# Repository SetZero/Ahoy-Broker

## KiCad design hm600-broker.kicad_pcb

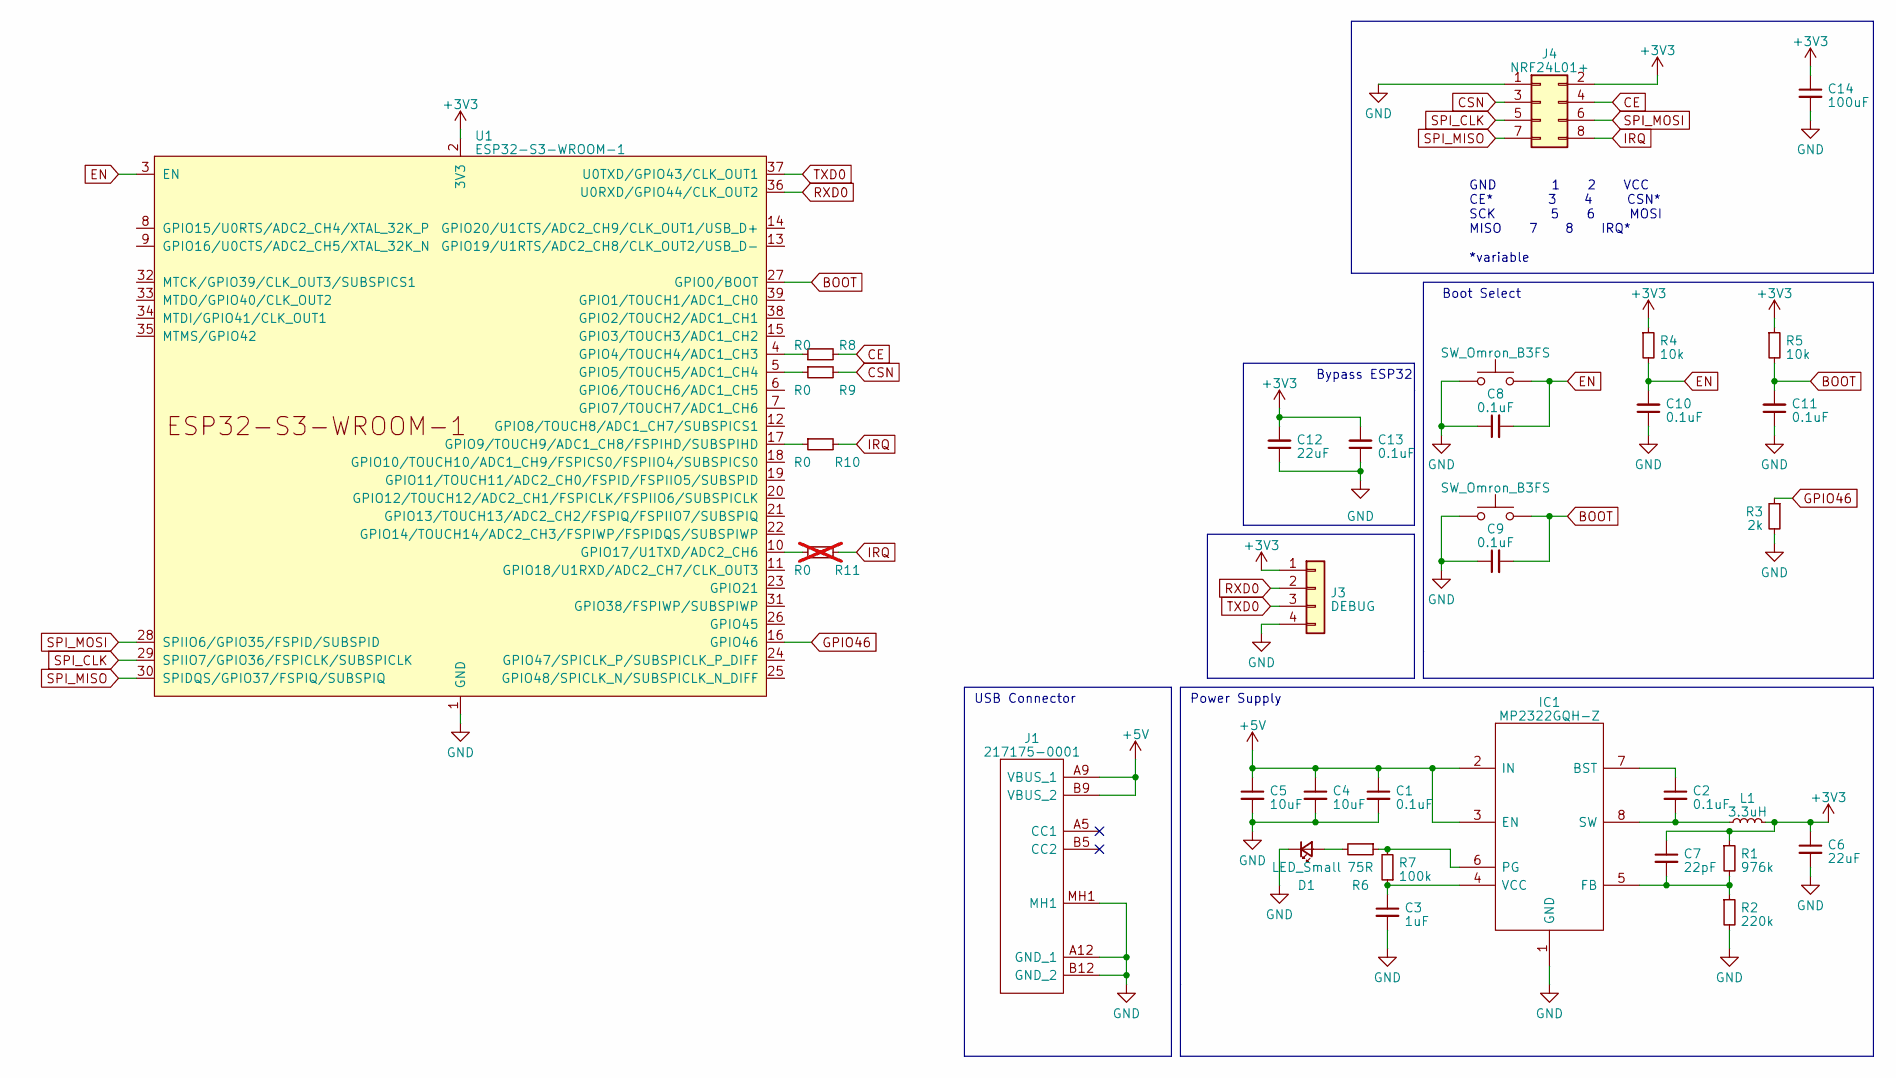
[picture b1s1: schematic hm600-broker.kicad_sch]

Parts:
C1, C2, C8, C9, C10, C11, C13: 0.1uF; C_0402_1005Metric
C3: 1uF; C_0402_1005Metric
C4, C5: 10uF; C_0805_2012Metric_Pad1.18x1.45mm_HandSolder
C6, C12: 22uF; C_0805_2012Metric_Pad1.18x1.45mm_HandSolder
C7: 22pF; C_0402_1005Metric
C14: 100uF; C_0805_2012Metric_Pad1.18x1.45mm_HandSolder
D1: LED_Small; LED_0805_2012Metric_Pad1.15x1.40mm_HandSolder
IC1: MP2322GQH-Z; MP2322GQHZ; Mouser Part Number 946-MP2322GQH-Z
J1: 217175-0001; 2171750001; Mouser Part Number 538-217175-0001
J3: DEBUG; PinHeader_1x04_P2.54mm_Vertical
J4: NRF24L01+; PinHeader_2x04_P2.54mm_Vertical
L1: 3.3uH; INDPM2424X100N
R1: 976k; R_0603_1608Metric_Pad0.98x0.95mm_HandSolder
R2: 220k; R_0603_1608Metric_Pad0.98x0.95mm_HandSolder
R3: 2k; R_0603_1608Metric_Pad0.98x0.95mm_HandSolder
R4, R5: 10k; R_0603_1608Metric_Pad0.98x0.95mm_HandSolder
R6: 75R; R_0603_1608Metric_Pad0.98x0.95mm_HandSolder
R7: 100k; R_0603_1608Metric_Pad0.98x0.95mm_HandSolder
R8, R9, R10: R0; R_0603_1608Metric_Pad0.98x0.95mm_HandSolder
R11: R0; R_0603_1608Metric_Pad0.98x0.95mm_HandSolder; not fitted
SW1, SW2: SW_Omron_B3FS; PTS636SP50SMTRLFS
U1: ESP32-S3-WROOM-1

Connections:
+3V3: C6.1, C7.1, C12.2, C13.2, C14.1, J3.1, J4.2, L1.2, R1.1, R4.1, R5.1, U1.2 (3V3)
+5V: C1.1, C4.1, C5.1, IC1.2 (IN), IC1.3 (EN), J1.A9 (VBUS_1), J1.B9 (VBUS_2)
BOOT: C9.2, C11.2, R5.2, SW1.2, U1.27 (GPIO0/BOOT)
CE: J4.4, R8.2
CSN: J4.3, R9.2
EN: C8.2, C10.2, R4.2, SW2.2, U1.3 (EN)
GND: C1.2, C3.2, C4.2, C5.2, C6.2, C8.1, C9.1, C10.1, C11.1, C12.1, C13.1, C14.2, D1.1 (K), IC1.1 (GND), J1.A12 (GND_1), J1.B12 (GND_2), J1.MH1, J1.MH2, J1.MH3, J1.MH4, J3.4, J4.1, R2.2, R3.2, SW1.1, SW2.1, U1.1 (GND), U1.40 (GND), U1.41 (GND)
GPIO46: R3.1, U1.16 (GPIO46)
IRQ: J4.8, R10.2, R11.2
unnamed: D1.2 (A), R6.2
unnamed: C2.1, IC1.7 (BST)
unnamed: C7.2, IC1.5 (FB), R1.2, R2.1
unnamed: IC1.6 (PG), R6.1, R7.2
unnamed: C2.2, IC1.8 (SW), L1.1
unnamed: C3.1, IC1.4 (VCC), R7.1
unnamed: R8.1, U1.4 (GPIO4/TOUCH4/ADC1_CH3)
unnamed: R9.1, U1.5 (GPIO5/TOUCH5/ADC1_CH4)
unnamed: R10.1, U1.17 (GPIO9/TOUCH9/ADC1_CH8/FSPIHD/SUBSPIHD)
unnamed: R11.1, U1.10 (GPIO17/U1TXD/ADC2_CH6)
RXD0: J3.2, U1.36 (U0RXD/GPIO44/CLK_OUT2)
SPI_CLK: J4.5, U1.29 (SPIIO7/GPIO36/FSPICLK/SUBSPICLK)
SPI_MISO: J4.7, U1.30 (SPIDQS/GPIO37/FSPIQ/SUBSPIQ)
SPI_MOSI: J4.6, U1.28 (SPIIO6/GPIO35/FSPID/SUBSPID)
TXD0: J3.3, U1.37 (U0TXD/GPIO43/CLK_OUT1)

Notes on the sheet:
Power Supply
Bypass ESP32
Boot Select
GND 1 2 VCC CE* 3 4 CSN* SCK 5 6 MOSI MISO 7 8 IRQ* *variable
USB Connector

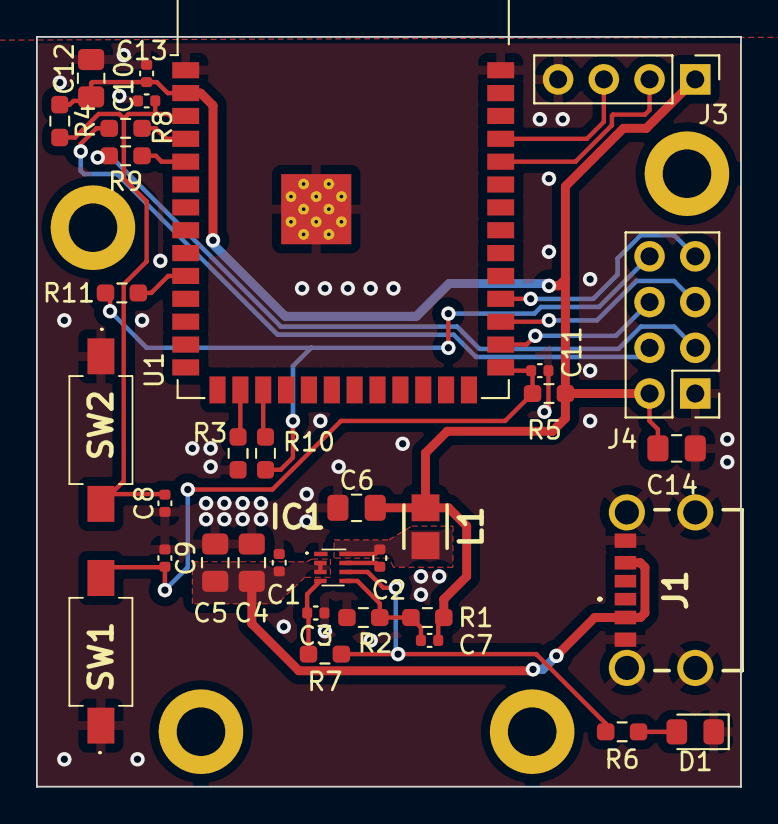
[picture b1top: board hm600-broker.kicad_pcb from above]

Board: 2 copper layers, 39.1 x 41.7 mm, 34 parts (0 on the bottom side), 24 nets.
